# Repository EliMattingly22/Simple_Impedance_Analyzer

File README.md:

# Simple Impedance Analyzer

## Purpose

The impedance analyzer was designed as a low-cost, flexible, and accurate platform to perform impedance measurement at arbitrary frequencies up to ~250kHz. The current infrastructure assumes the user has access to a National Instruments DAQ (e.g. NI-USB-6363), though similar digitizers would be similarly effective. 

In this current configuration:
* About 0.1% Accuracy for large impedance and frequency ranges.
* The LabView has an easy to use GUI
* TDMS file saving
* It can measure impedances from 10mOhms to 10MOhms, and by changing the shunt resistor values that range could be extended 
* Test at frequencies from DC-250kHz (>100kHz still needs validation)
* Perform frequency sweeps on log or linear spacing
* If a battery-powered computer and DAQ is used, the entire measurement apparatus can be both portable and floating.

### Accuracy and noise (1 kHz resistive)

### Accuracy and noise (10 kHz resistive)

### Accuracy and noise (100 kHz resistive)

### Accuracy and noise (10 kHz Capacitors)

* It seems one can expect about 1% accuracy between 10 p to 0.1 mF. 
* The point indicating 0.01% accuracy is probably spurious. Some random errors happened to offset each others. 

# PCB
Use V2 rev B. V3 has not been tested/built. it is still in design phase. Perhaps it should just be in a separate brach of Github. Designed in KiCAD v6.

# Operating Principle
This circuit uses the "auto-balancing bridge" technique. If you are curious/want to play around with the circuit you can see the LTSPICE schematic. 

It is worth reading the [Keysight impedance measurement handbook](https://www.keysight.com/us/en/assets/7018-06840/application-notes/5950-3000.pdf) or TI's reference design for an LCR meter front-end for an overview of measurement techniques. 

The current through the DUT is (ideally) the same as the current in the shunt resistor, so the impedance is V(DUT) / (V(Shunt)/R(Shunt)). 

# Source of Errors

The precision of the circuit is dominated by the shunt resistors and gain accuracy of the INAs. Error in any of these will linearly cause an error in the calculated impedance. If they are stable over time, they can conceivably be calibrated with a high tolerance (e.g. 0.01%) reference resistor.

If the shunt resistor is off by some value, *X* (where 1.01 would be 1% higher than nominal), the current would be reported as I<sub>0</sub>**X* where I<sub>0</sub> is the actual current. 

The noise performance of the INAs isn't great, but the FET inputs have extremely low bias currents, and low current noise, which are necessary if high impedance loads are attached. The noise should add an incoherent error, so by averaging for longer, this can be mitigated. 

The parasitic elements can be accounted for by taking an open/short/load measurement. See sect. 4.3.2 in the impedance measurement handbook

# Operation instructions
## Setup
The device should be plugged in with a four-wire (Kelvin) probe attached. On the probe there will be two pairs of leads, each connected to a clamp (typically one pair is red, one is black). The two BNC connections on the red lead should be plugged into the "HPot" and "HCur" connectors, and the BNCs on the black probe should be connected to "LPot" and "HPot" connectors. 

Plug in the power and make sure the LEDs next to the "+5V" and "-5V" are illuminated. 

The DAQ should be plugged in via the BNC connectors and however they are connected, those outputs/inputs are selected on the front page of the Labview GUI.

Also on the front page, set the sampling rate to the maximum allowable (see documentation for your DAQ). Set the sampling time to be >10 periods of whatever frequency you are testing at. Longer gives better noise performance.

For the shunt resistor, use the value most similar to the load you are measuring. Use J13/14 to select the shunt resistor. 

Set the series resistor before the load (R9/24) to the same value as the shunt resistor using J17.

* For the saving cluster the Fine Name String will be the identifier in the file name.
* Save path is the directory it will be saved within
* Experiment title is a string added to the metadata
* Meta-data array is an array that the user can fill in as desired. It just goes into meta-data as-is. For example, if you are measuring the turns on an inductor vs inductance, you could enter the turn count in this spot and then afterwards when processing the data it would already be saved. 

* **Test Freq:** This is the measurement frequency for single measurements and stats. It is overwritten for frequency sweeps.
* **Output Signal Amp:** This is the waveform amplitude the DAQ outputs. If this is too low, SNR is sacrificed, if it is too high, the waveform can clip. Check the debugging cluster to ensure the amplitude of the voltage monitor and current monitor arent clipping (i.e. they are less than 7 V or so)
* **Sampling time:** Time of acquisition in seconds. Should be long enough for 10 or so periods of the output waveform. More improves SNR. 
* **Sampling Rate:** Sampling rate in Hz. should be maximum allowable.
* **Output Channel:** The channel that goes into the Voltage Input BNC (top left in photo above)
* **Current Channel:** The channel that comes from the current sense BNC (Bottom left in photo above)
* **Voltage channel:** The channel that comes from the voltage sense BNC (middle left in photo above)
* **Trigger channel:** This should be set to the output start trigger, for example "/Dev2/ao/StartTrigger"
* **Number of runs:** this is the number of times the acquisition will be repeated and averaged.

* **R_Shunt:** The shunt resistor value (R14/18)
* **Rg_Vmon:** The gain-setting resistor for the voltage monitor (R12 or R8) 
* **Rg_Imon:** The gain-setting resistor for the current monitor (R11 or R7) 
* **ESL_Cal:** This value is set by the short circuit compensation and is enabled by the UseCorrection boolean
* **ESR_Cal:** This value is set by the short circuit compensation and is enabled by the UseCorrection boolean
* **Cp_Cal:** This value is set by the open circuit compensation and is enabled by the UseCorrection boolean
* **Rp_Cal:** This value is set by the open circuit compensation and is enabled by the UseCorrection boolean

* **UseCorrection:** enables the short/open compensation values. Typically set to TRUE (green illuminated)

* **RLoad:** This is the actual value of the load compensation resistor that one may use to calibrate gain errors of the system. 

* **RLoad_Meas:** This is the measured value of that load. To acquire this value, set RLoad and RLoad_Meas to 0 and then measure the known load and set this and the RLoad by typing in the appropriate values.

## Calibration

Set the equipment up to measure your load, and short the clips together. Next, go to the Short/Open compensation tab and press the "Acquire short" button. Open the clips and then do the open compensation.

## Measure load

Use the last page to do a single impedance measurement and ensure the load is similar to expected. Then use the stats page or freq sweep depending on what you want. 

## List of jumpers & their purpose
* J15/16 low-pass filters for the input. These clean the analog signal from the DAQ. They can generally be set to the highest frequency that the user plans to measure. Removing the jumper disconnects the filtering entirely.

* J10: The current monitor gain selection
* J12: Voltage monitor gain selection
* J13/14: Shunt resistor selection
* J17: Series resistor selection. This resistor in series with the load helps stability and makes the system more balanced. The resistor value should match the shunt resistor value.

# If you are having errors:
1) Make sure the channels are selected properly
2) Make sure BOTH sides of the clips are on the load
3) Make sure the BNCs are properly attached
4) The LEDs should be illuminated
5) The amplitude should be sufficiently low that it doesn't saturate the inputs/clip

# Example applications:

## Litz wire, air-core inductor

* The impedance is exactly as expected here for an inductor. Because Litz wire was used, the resistance is not a strong function of frequency. 
* The slope of the reactance is constant and proportional to frequency.

## Skin and proximity effect on inductor

This is a frequency sweep of a solenoid (~1 mm diameter) wound on a copper tube with a wall-thickness of ~1 mm. Quite a lot is happening with this load:
* Below 50 Hz or so, it is essentially a resistor, the inductive impedance is very small. 
* At 50-1k Hz, the solenoid's impedance has an increasing real component and decreasing inductance (decreasing slope of imag.). This occurs as the inductor couples more strongly into the copper tube. The inductance decreases because the magnetic field in the center of the tube is decreasing as the wall effectively shields it. 
* Between 1k and 10k Hz the resistance nearly plateaus and the inductance starts rising proportionally to frequency. Presumably at this point, the skin depth of the copper tube has been met, so the magnetic fields are not significantly penetrating to the center of the tube. 
* Above 10 kHz the skin depth of the wire is being reached and the AC-resistance is increasing as the effective copper area for current to flow in decreases.

## Resonant L-C

## Notch filter input

# Thoughts for improvement
* Make the shunt resistor digitally selectable
* Build a microcontroller-based interface for increased portability
* Improve system accuracy for high impedance loads
* Improve system accuracy for high frequencies
* Modify it such that it uses only one amplifier for both VMon and IMon and a relay to select which one. 
* Replace INA121 with a JFET INA (e.g. 3 opamp configuration)
* Implement transformer test jig

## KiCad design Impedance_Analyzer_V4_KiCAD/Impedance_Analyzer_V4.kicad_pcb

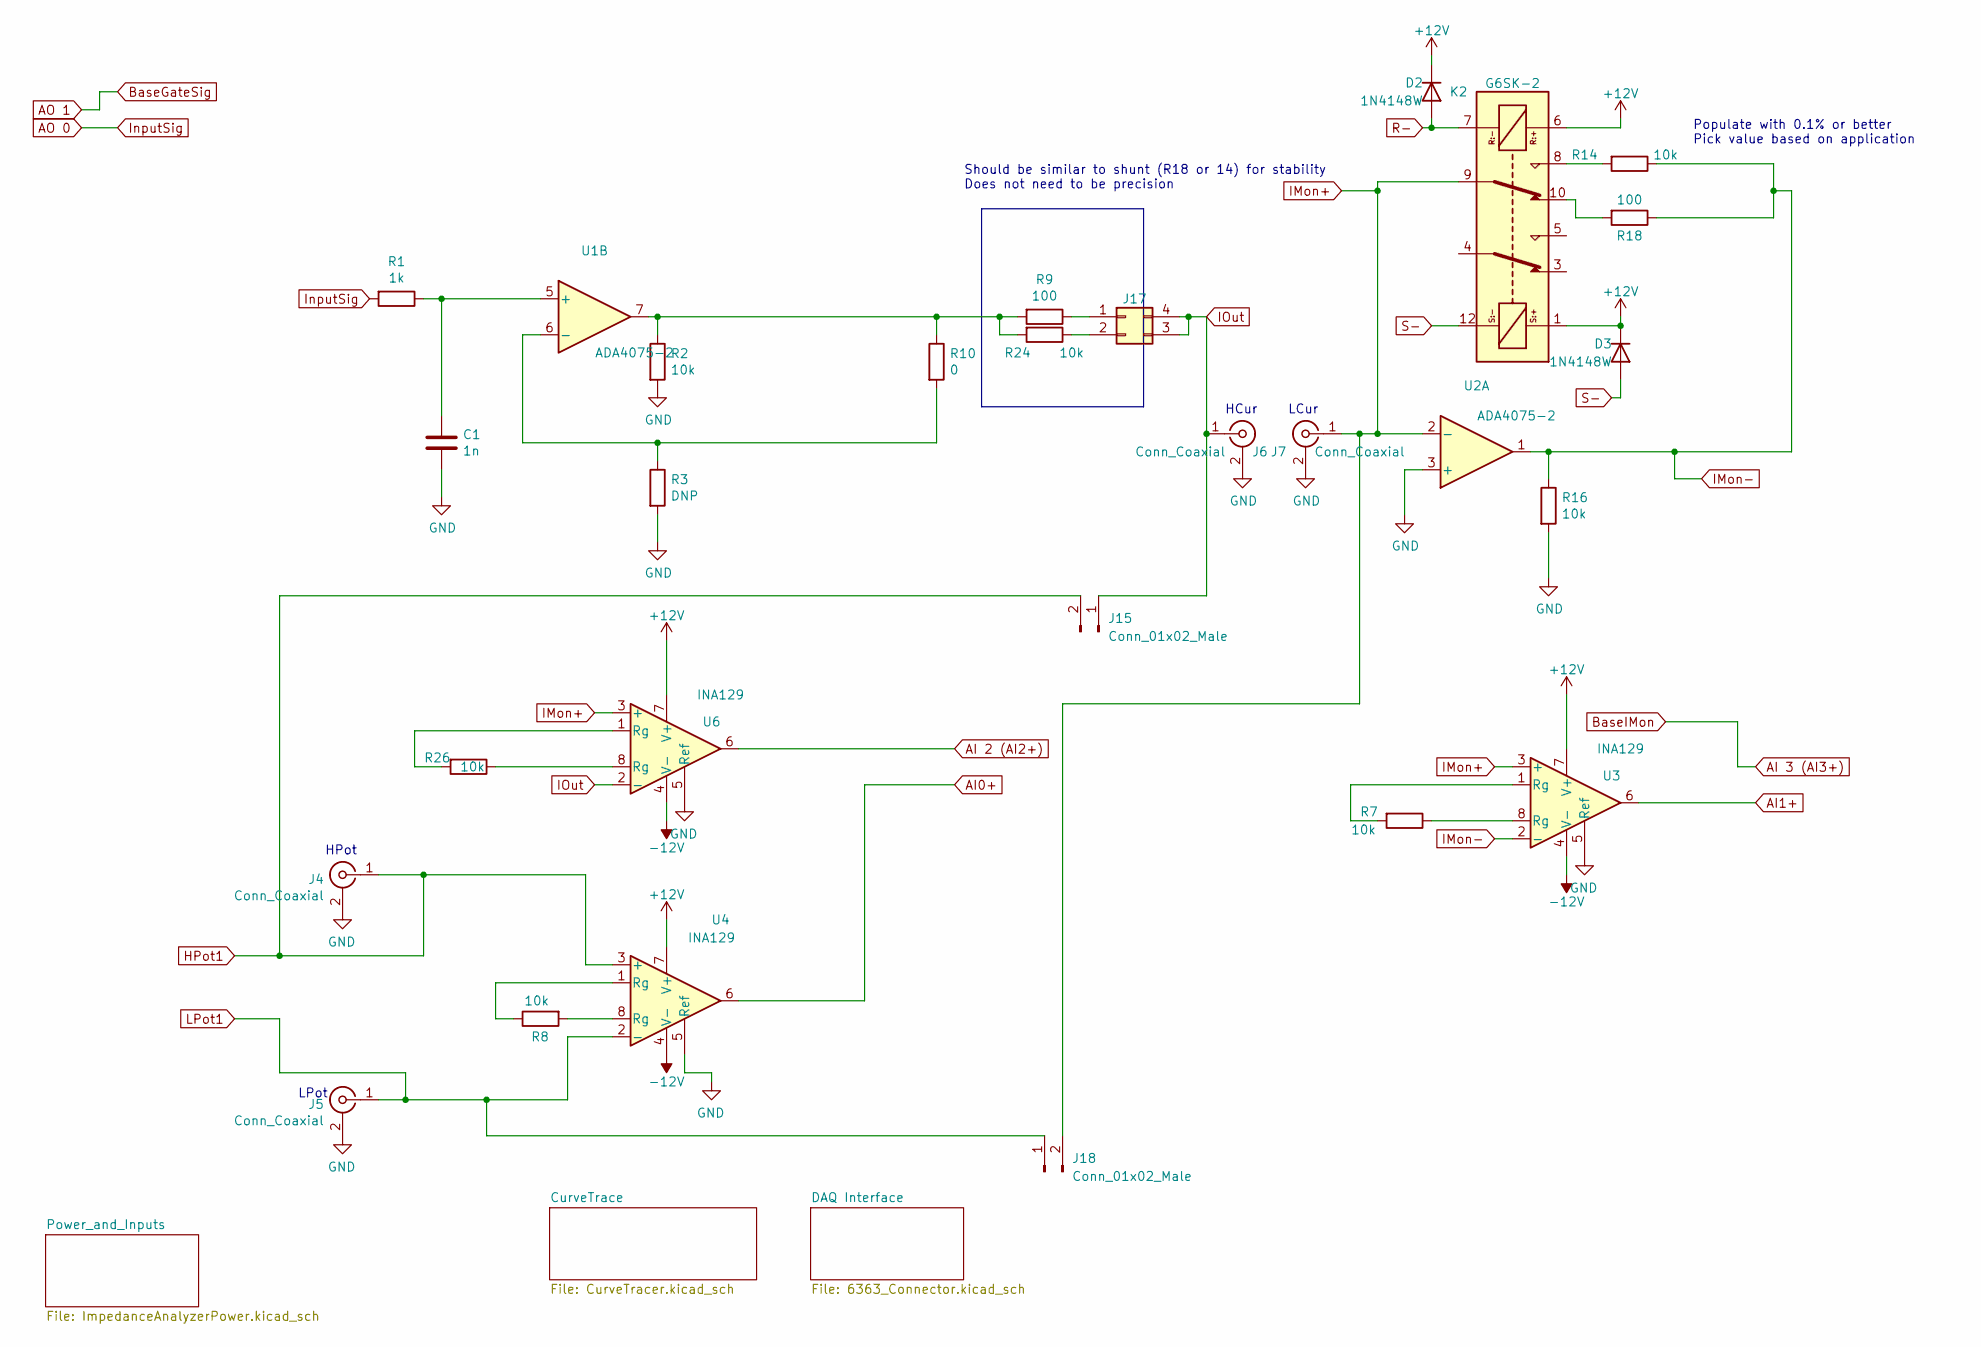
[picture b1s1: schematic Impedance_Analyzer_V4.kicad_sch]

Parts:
C1: 1n; C_0805_2012Metric
D2, D3: 1N4148W; D_SOD-123
J4, J5, J6, J7: Conn_Coaxial; 31-5486-1010 BNC Panel RA
J15, J18: Conn_01x02_Male; PinHeader_1x02_P2.54mm_Horizontal
J17: Conn_02x02_Counter_Clockwise; PinHeader_2x02_P2.54mm_Vertical
K2: G6SK-2; RELAY_G6SK-2F DC3_OMR
R1: 1k; R_1206_3216Metric
R2, R7, R8, R14, R16, R24, R26: 10k; R_1206_3216Metric
R3: DNP; R_1206_3216Metric
R9, R18: 100; R_1206_3216Metric
R10: 0; R_1206_3216Metric
U1, U2: ADA4075-2; SO-8_3.9x4.9mm_P1.27mm
U3, U4, U6: INA129; DIP-8_W7.62mm

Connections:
+12V: D2.1 (K), D3.1 (K), K2.1, K2.6, U3.7 (V+), U4.7 (V+), U6.7 (V+); also elsewhere on the board
-12V: U3.4 (V-), U4.4 (V-), U6.4 (V-); also elsewhere on the board
AI0+: U4.6; also elsewhere on the board
AI1+: U3.6; also elsewhere on the board
AI 2 (AI2+): U6.6; also elsewhere on the board
AO 0: R1.2; also elsewhere on the board
GND: C1.2, J4.2 (Ext), J5.2 (Ext), J6.2 (Ext), J7.2 (Ext), R2.2, R3.2, R16.2, U2.3 (+), U3.5 (Ref), U4.5 (Ref), U6.5 (Ref); also elsewhere on the board
HPot1: J4.1 (In), J15.2, U4.3 (+); also elsewhere on the board
IMon+: J7.1 (In), J18.2, K2.9, U2.2 (-), U3.3 (+), U6.3 (+)
IMon-: R14.1, R16.1, R18.1, U2.1, U3.2 (-)
IOut: J6.1 (In), J15.1, J17.3, J17.4, U6.2 (-)
LPot1: J5.1 (In), J18.1, U4.2 (-); also elsewhere on the board
unnamed: C1.1, R1.1, U1.5 (+)
unnamed: J17.1, R9.1
unnamed: J17.2, R24.1
unnamed: K2.8, R14.2
unnamed: K2.10, R18.2
unnamed: R7.1, U3.8 (Rg)
unnamed: R7.2, U3.1 (Rg)
unnamed: R8.1, U4.1 (Rg)
unnamed: R8.2, U4.8 (Rg)
unnamed: R2.1, R9.2, R10.1, R24.2, U1.7
unnamed: R3.1, R10.2, U1.6 (-)
unnamed: R26.1, U6.8 (Rg)
unnamed: R26.2, U6.1 (Rg)
R-: D2.2 (A), K2.7; also elsewhere on the board
S-: D3.2 (A), K2.12; also elsewhere on the board

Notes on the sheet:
HCur
Should be similar to shunt (R18 or 14) for stability Does not need to be precision
LCur
LPot
HPot
Populate with 0.1% or better Pick value based on application

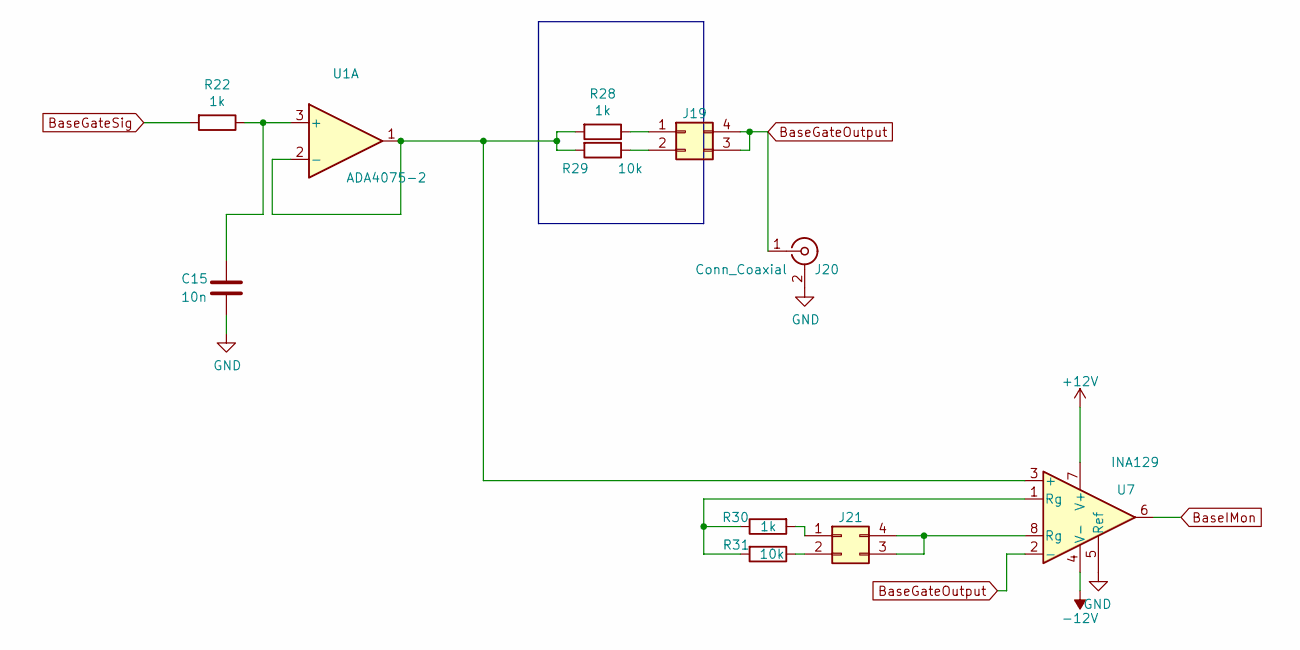
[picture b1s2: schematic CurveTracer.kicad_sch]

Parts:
C15: 10n; C_0805_2012Metric
J19, J21: Conn_02x02_Counter_Clockwise; PinHeader_2x02_P2.54mm_Vertical
J20: Conn_Coaxial; 31-5486-1010 BNC Panel RA
R22, R28, R30: 1k; R_1206_3216Metric
R29, R31: 10k; R_1206_3216Metric
U1: ADA4075-2; SO-8_3.9x4.9mm_P1.27mm
U7: INA129; DIP-8_W7.62mm

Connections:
+12V: U7.7 (V+); also elsewhere on the board
-12V: U7.4 (V-); also elsewhere on the board
BaseGateOutput: J19.3, J19.4, J20.1 (In), U7.2 (-)
GND: C15.2, J20.2 (Ext), U7.5 (Ref); also elsewhere on the board
unnamed: C15.1, R22.1, U1.3 (+)
unnamed: J19.1, R28.1
unnamed: J19.2, R29.1
unnamed: J21.1, R30.2
unnamed: J21.2, R31.1
unnamed: J21.3, J21.4, U7.8 (Rg)
unnamed: R28.2, R29.2, U1.1, U1.2 (-), U7.3 (+)
unnamed: R30.1, R31.2, U7.1 (Rg)

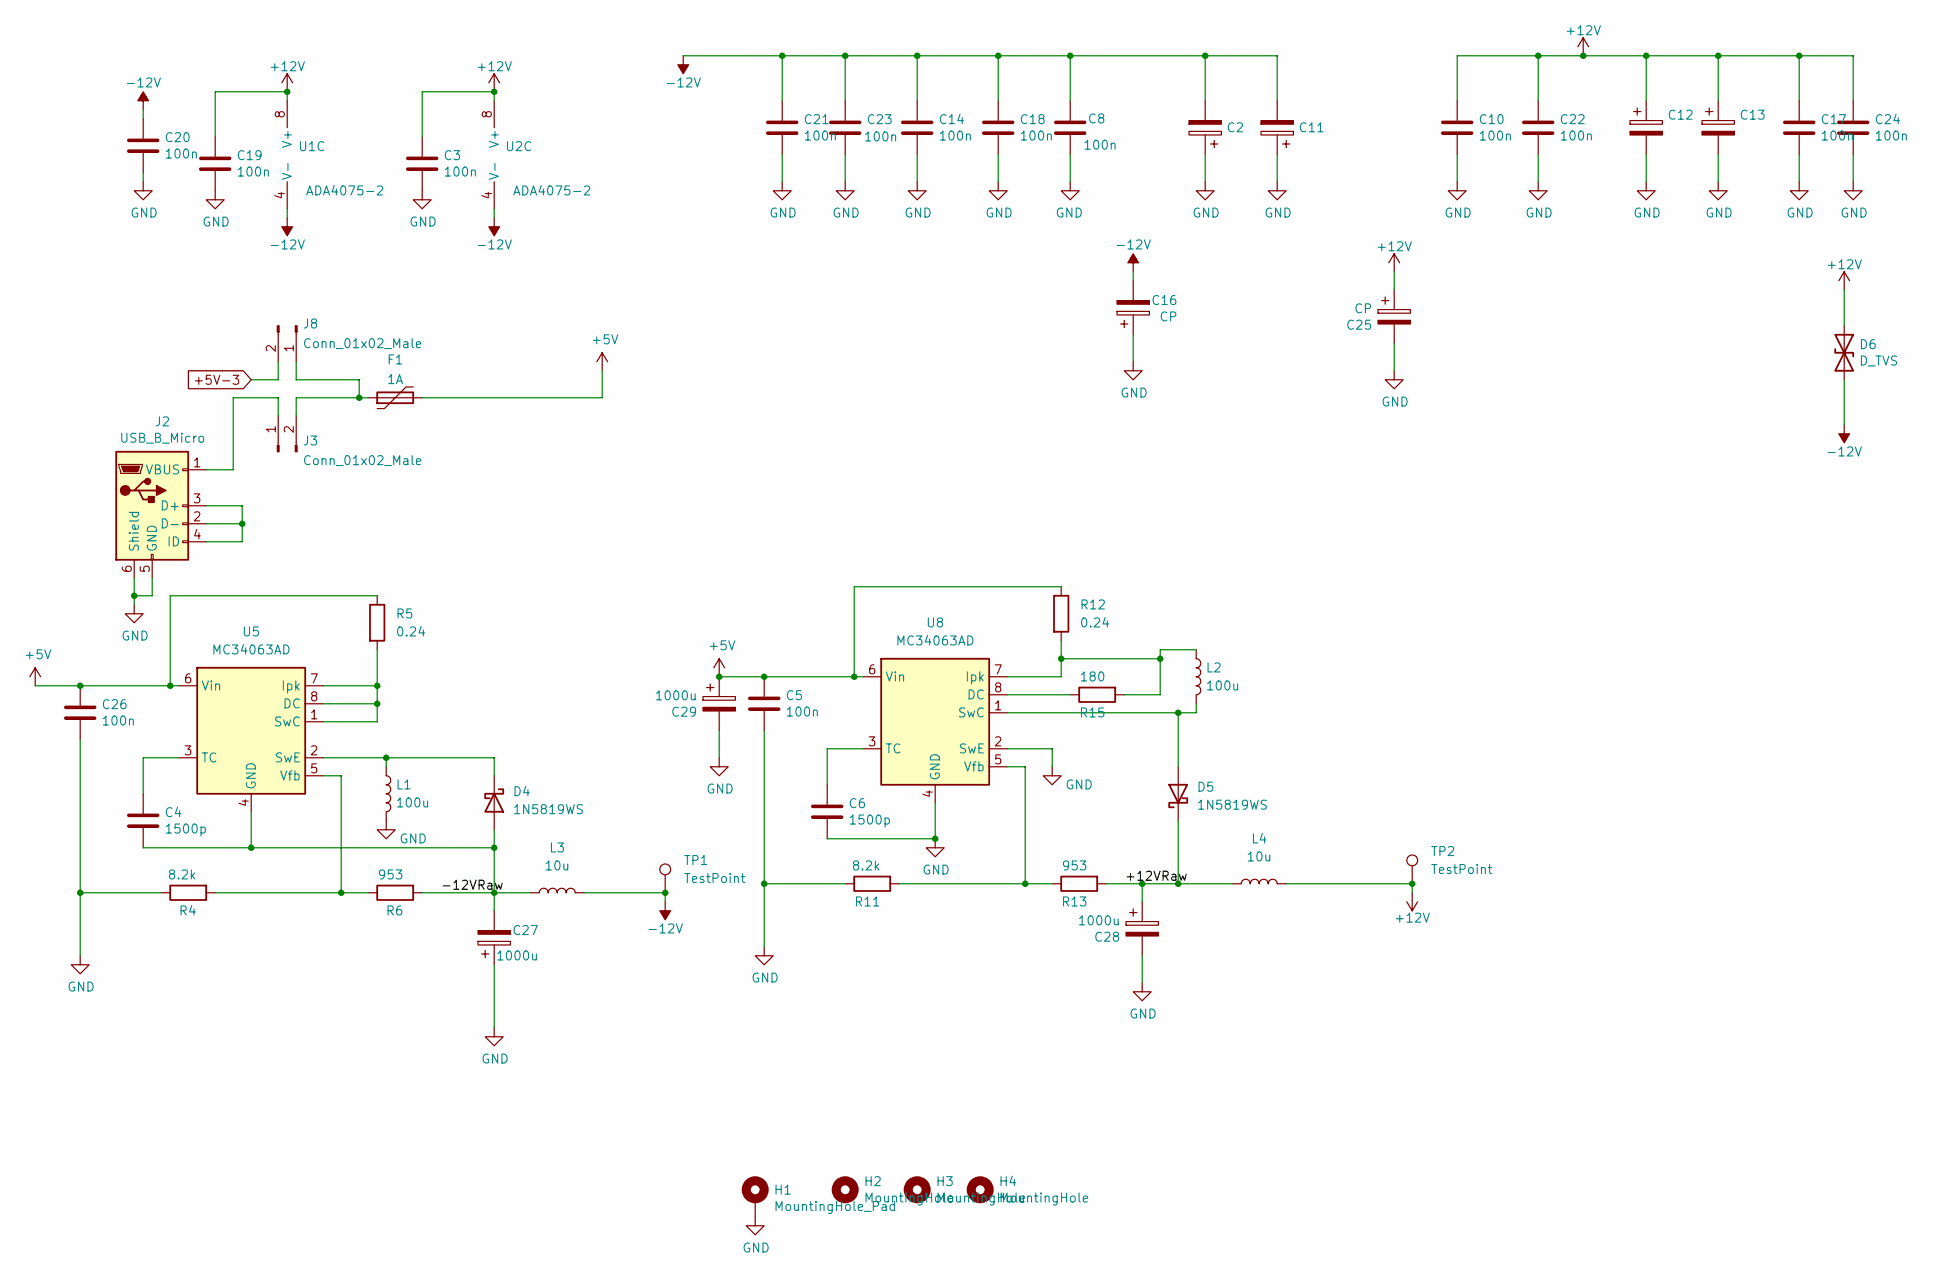
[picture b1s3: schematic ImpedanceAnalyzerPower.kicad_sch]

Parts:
C2, C11, C12, C13: C_Polarized; C_1206_3216Metric_Pad1.33x1.80mm_HandSolder
C3, C5, C8, C10, C14, C17, C18, C19, C20, C21, C22, C23, C24, C26: 100n; C_0805_2012Metric
C4, C6: 1500p; C_0805_2012Metric
C16, C25: CP; CP_Radial_D8.0mm_P5.00mm
C27, C28, C29: 1000u; CP_Elec_10x10.5
D4, D5: 1N5819WS; D_SOD-323
D6: D_TVS; D_SMA
F1: 1A; Fuse_1206_3216Metric_Pad1.42x1.75mm_HandSolder
H1: MountingHole_Pad; MountingHole_4.3mm_M4_Pad
H2, H3, H4: MountingHole; MountingHole_4mm
J2: USB_B_Micro; AMPHENOL_10118194-0001LF
J3, J8: Conn_01x02_Male; PinHeader_1x02_P2.54mm_Vertical
L1, L2: 100u; L_Taiyo-Yuden_NR-80xx_HandSoldering
L3, L4: 10u; L_Taiyo-Yuden_NR-60xx_HandSoldering
R4, R11: 8.2k; R_1206_3216Metric
R5, R12: 0.24; R_1206_3216Metric
R6, R13: 953; R_1206_3216Metric
R15: 180; R_1206_3216Metric
TP1, TP2: TestPoint; TestPoint_THTPad_2.0x2.0mm_Drill1.0mm
U1, U2: ADA4075-2; SO-8_3.9x4.9mm_P1.27mm
U5, U8: MC34063AD; SOIC-8_3.9x4.9mm_P1.27mm

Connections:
+5V: C5.1, C26.1, C29.1, F1.2, R5.1, R12.1, U5.6 (Vin), U8.6 (Vin); also elsewhere on the board
+5V-3: J8.2; also elsewhere on the board
+12V: C3.1, C10.1, C12.1, C13.1, C17.1, C19.1, C22.1, C24.1, C25.1, D6.1 (A1), L4.2, TP2.1, U1.8 (V+), U2.8 (V+); also elsewhere on the board
-12V: C2.2, C8.1, C11.2, C14.1, C16.2, C18.1, C20.1, C21.1, C23.1, D6.2 (A2), L3.2, TP1.1, U1.4 (V-), U2.4 (V-); also elsewhere on the board
/Power_and_Inputs/+12VRaw: C28.1, D5.1 (K), L4.1, R13.2
/Power_and_Inputs/-12VRaw: C4.2, C27.2, D4.2 (A), L3.1, R6.2, U5.4 (GND)
GND: C2.1, C3.2, C5.2, C6.2, C8.2, C10.2, C11.1, C12.2, C13.2, C14.2, C16.1, C17.2, C18.2, C19.2, C20.2, C21.2, C22.2, C23.2, C24.2, C25.2, C26.2, C27.1, C28.2, C29.2, H1.1, J2.5 (GND), J2.6 (Shield), L1.2, R4.1, R11.1, U8.2 (SwE), U8.4 (GND); also elsewhere on the board
unnamed: C4.1, U5.3 (TC)
unnamed: C6.1, U8.3 (TC)
unnamed: D4.1 (K), L1.1, U5.2 (SwE)
unnamed: D5.2 (A), L2.2, U8.1 (SwC)
unnamed: F1.1, J3.2, J8.1
unnamed: J2.1 (VBUS), J3.1
unnamed: J2.2 (D-), J2.3 (D+), J2.4 (ID)
unnamed: L2.1, R12.2, R15.2, U8.7 (Ipk)
unnamed: R4.2, R6.1, U5.5 (Vfb)
unnamed: R5.2, U5.1 (SwC), U5.7 (Ipk), U5.8 (DC)
unnamed: R11.2, R13.1, U8.5 (Vfb)
unnamed: R15.1, U8.8 (DC)

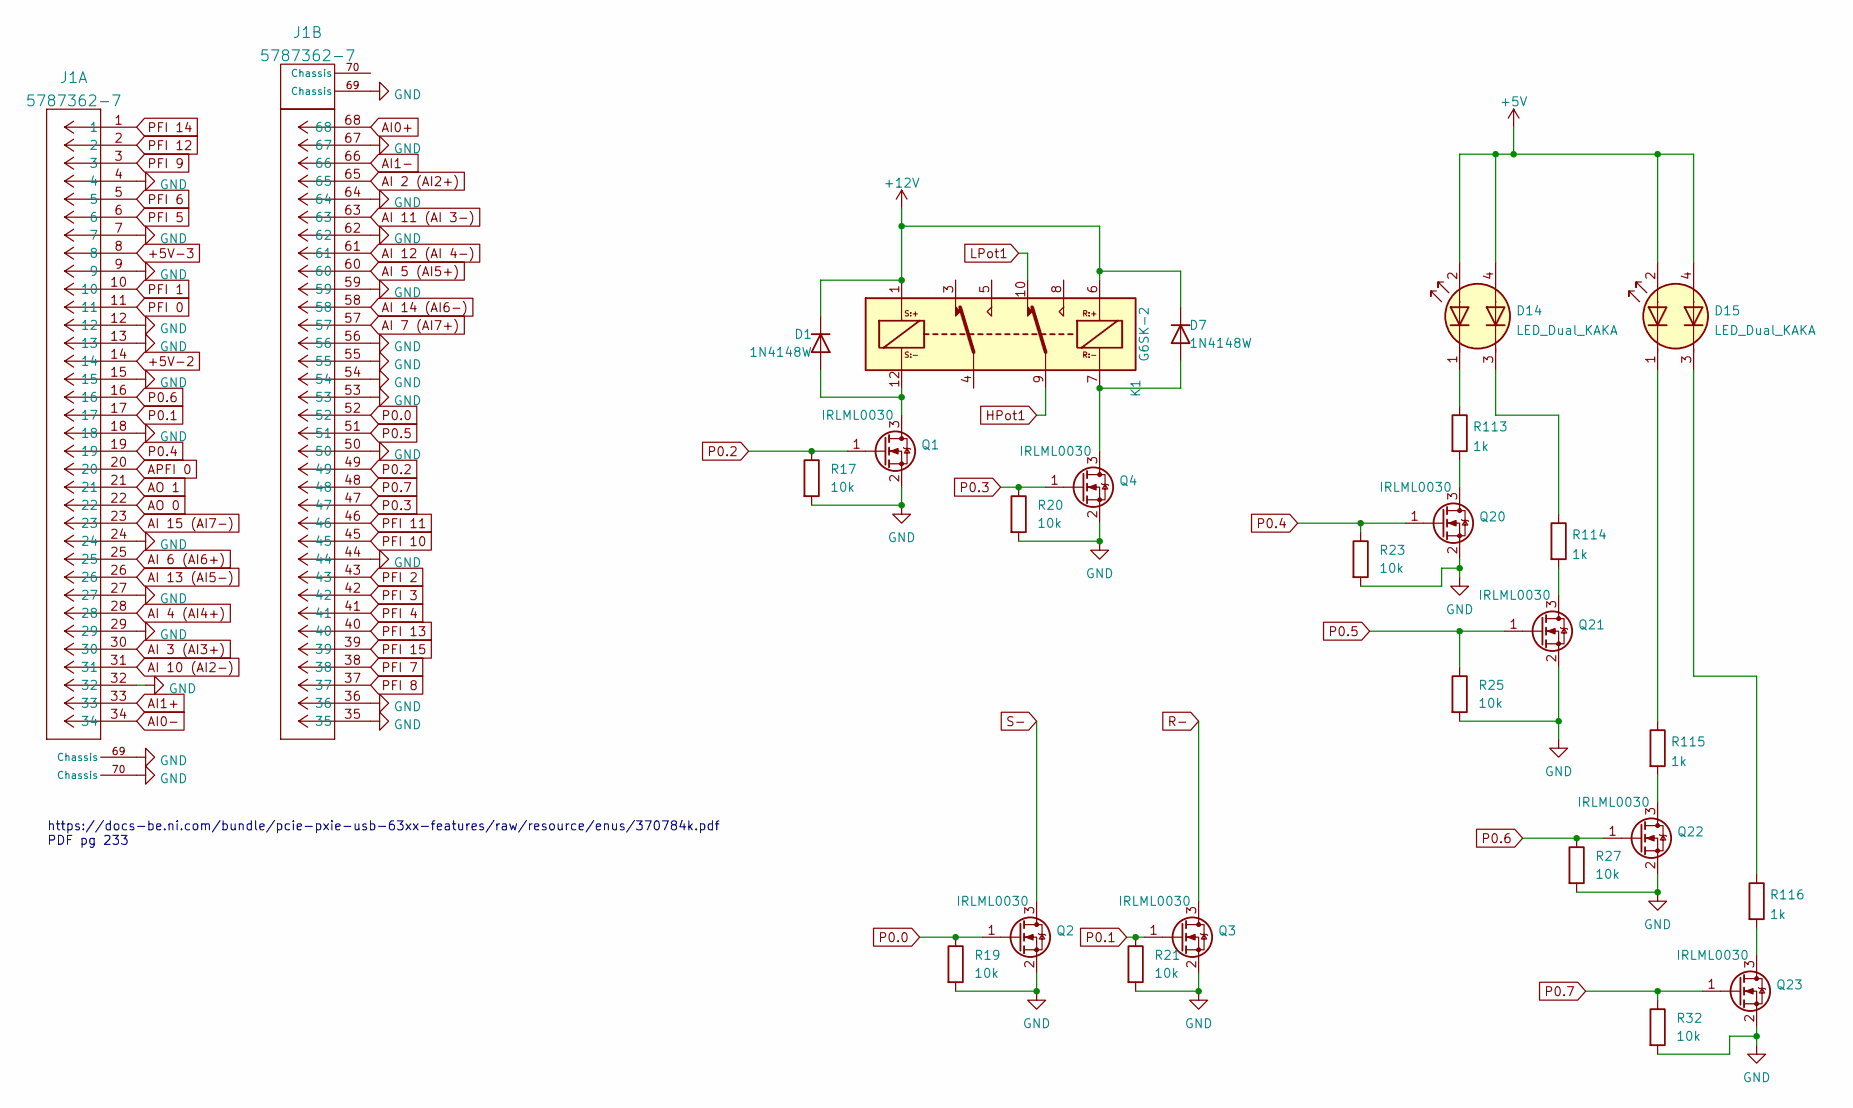
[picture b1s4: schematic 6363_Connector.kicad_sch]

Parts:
D1, D7: 1N4148W; D_SOD-123
D14, D15: LED_Dual_KAKA; IC4_WP934EB_2GD_KNB
J1: 5787362-7; 68DsubMaleTE_2-5174225-5
K1: G6SK-2; RELAY_G6SK-2F DC3_OMR
Q1, Q2, Q3, Q4, Q20, Q21, Q22, Q23: IRLML0030; SOT-23
R17, R19, R20, R21, R23, R25, R27, R32: 10k; R_0805_2012Metric_Pad1.20x1.40mm_HandSolder
R113, R114, R115, R116: 1k; R_0805_2012Metric_Pad1.20x1.40mm_HandSolder

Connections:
+5V: D14.2 (K1), D14.4 (K2), D15.2 (K1), D15.4 (K2); also elsewhere on the board
+5V-2: J1.14
+5V-3: J1.8; also elsewhere on the board
+12V: D1.1 (K), D7.1 (K), K1.1, K1.6; also elsewhere on the board
AI0+: J1.68; also elsewhere on the board
AI0-: J1.34
AI1+: J1.33; also elsewhere on the board
AI1-: J1.66
AI 2 (AI2+): J1.65; also elsewhere on the board
AI 4 (AI4+): J1.28
AI 5 (AI5+): J1.60
AI 6 (AI6+): J1.25
AI 7 (AI7+): J1.57
AI 10 (AI2-): J1.31
AI 11 (AI 3-): J1.63
AI 12 (AI 4-): J1.61
AI 13 (AI5-): J1.26
AI 14 (AI6-): J1.58
AI 15 (AI7-): J1.23
AO 0: J1.22; also elsewhere on the board
APFI 0: J1.20
GND: J1.4, J1.7, J1.9, J1.12, J1.13, J1.15, J1.18, J1.24, J1.27, J1.29, J1.32, J1.35, J1.36, J1.44, J1.50, J1.53, J1.54, J1.55, J1.56, J1.59, J1.62, J1.64, J1.67, J1.69 (Chassis), J1.70 (Chassis), Q1.2 (S), Q2.2 (S), Q3.2 (S), Q4.2 (S), Q20.2 (S), Q21.2 (S), Q22.2 (S), Q23.2 (S), R17.2, R19.2, R20.2, R21.2, R23.2, R25.2, R27.2, R32.2; also elsewhere on the board
HPot1: K1.9; also elsewhere on the board
LPot1: K1.10; also elsewhere on the board
unnamed: D1.2 (A), K1.12, Q1.3 (D)
unnamed: D7.2 (A), K1.7, Q4.3 (D)
unnamed: D14.1 (A1), R113.1
unnamed: D14.3 (A2), R114.1
unnamed: D15.1 (A1), R115.1
unnamed: D15.3 (A2), R116.1
unnamed: Q20.3 (D), R113.2
unnamed: Q21.3 (D), R114.2
unnamed: Q22.3 (D), R115.2
unnamed: Q23.3 (D), R116.2
P0.0: J1.52, Q2.1 (G), R19.1
P0.1: J1.17, Q3.1 (G), R21.1
P0.2: J1.49, Q1.1 (G), R17.1
P0.3: J1.47, Q4.1 (G), R20.1
P0.4: J1.19, Q20.1 (G), R23.1
P0.5: J1.51, Q21.1 (G), R25.1
P0.6: J1.16, Q22.1 (G), R27.1
P0.7: J1.48, Q23.1 (G), R32.1
PFI 0: J1.11
PFI 1: J1.10
PFI 2: J1.43
PFI 3: J1.42
PFI 4: J1.41
PFI 5: J1.6
PFI 6: J1.5
PFI 7: J1.38
PFI 8: J1.37
PFI 9: J1.3
PFI 10: J1.45
PFI 11: J1.46
PFI 12: J1.2
PFI 13: J1.40
PFI 14: J1.1
PFI 15: J1.39
R-: Q3.3 (D); also elsewhere on the board
S-: Q2.3 (D); also elsewhere on the board

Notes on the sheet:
https://docs-be.ni.com/bundle/pcie-pxie-usb-63xx-features/raw/resource/enus/370784k.pdf PDF pg 233

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
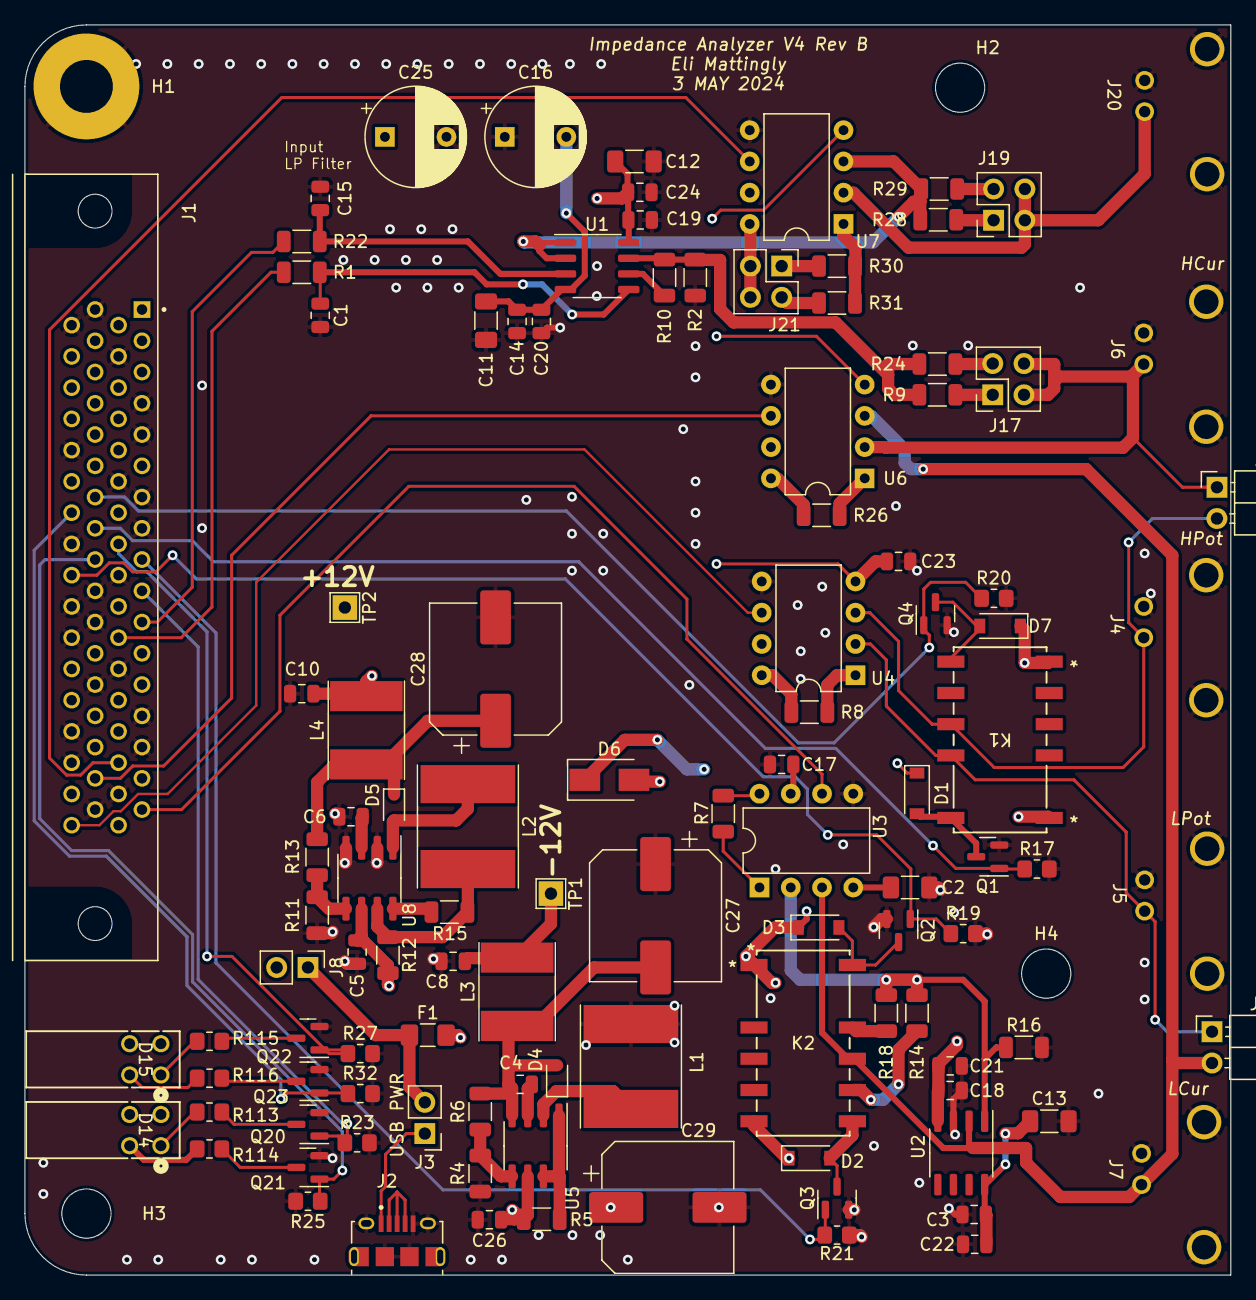
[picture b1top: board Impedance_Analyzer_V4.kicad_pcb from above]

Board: 4 copper layers, 98.0 x 101.6 mm, 114 parts (0 on the bottom side), 72 nets.

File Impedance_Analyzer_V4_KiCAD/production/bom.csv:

Designator,Footprint,Quantity,Value,LCSC Part #
C1,0805,1,1n,
C10,0805,1,100n,
C11,1206,1,C_Polarized,
C12,1206,1,C_Polarized,
C13,1206,1,C_Polarized,
C14,0805,1,100n,
C15,0805,1,10n,
"C16, C25",CP_Radial_D8.0mm_P5.00mm,2,CP,
C17,0805,1,100n,
C18,0805,1,100n,
C19,0805,1,100n,
C2,1206,1,C_Polarized,
C20,0805,1,100n,
C21,0805,1,100n,
C22,0805,1,100n,
C23,0805,1,100n,
C24,0805,1,100n,
C26,0805,1,100n,
"C27, C28, C29",CP_Elec_10x10.5,3,1000u,
C3,0805,1,100n,
C4,0805,1,1500p,
C5,0805,1,100n,
C6,0805,1,1500p,
C8,0805,1,100n,
"D1, D2, D3, D7",D_SOD-123,4,1N4148W,
"D14, D15",IC4_WP934EB_2GD_KNB,2,LED_Dual_KAKA,
"D4, D5",D_SOD-323,2,1N5819WS,
D6,D_SMA,1,D_TVS,
F1,1206,1,1A,
H1,MountingHole_4.3mm_M4_Pad,1,MountingHole_Pad,
"H2, H3, H4",MountingHole_4mm,3,MountingHole,
J1,68DsubMaleTE_2-5174225-5,1,5787362-7,
"J15, J18",PinHeader_1x02_P2.54mm_Horizontal,2,Conn_01x02_Male,
"J17, J19, J21",PinHeader_2x02_P2.54mm_Vertical,3,Conn_02x02_Counter_Clockwise,
J2,AMPHENOL_10118194-0001LF,1,USB_B_Micro,
"J20, J4, J5, J6, J7",31-5486-1010 BNC Panel RA,5,Conn_Coaxial,
"J3, J8",PinHeader_1x02_P2.54mm_Vertical,2,Conn_01x02_Male,
"K1, K2",RELAY_G6SK-2F DC3_OMR,2,G6SK-2,
"L1, L2",L_Taiyo-Yuden_NR-80xx_HandSoldering,2,100u,
"L3, L4",L_Taiyo-Yuden_NR-60xx_HandSoldering,2,10u,
"Q1, Q2, Q20, Q21, Q22, Q23, Q3, Q4",SOT-23,8,IRLML0030,
R1,1206,1,1k,
R10,1206,1,0,
R11,1206,1,8.2k,
R113,0805,1,1k,
R114,0805,1,1k,
R115,0805,1,1k,
R116,0805,1,1k,
R12,1206,1,0.24,
R13,1206,1,953,
R14,1206,1,10k,
R15,1206,1,180,
R16,1206,1,10k,
R17,0805,1,10k,
R18,1206,1,100,
R19,0805,1,10k,
R2,1206,1,10k,
R20,0805,1,10k,
R21,0805,1,10k,
R22,1206,1,1k,
R23,0805,1,10k,
R24,1206,1,10k,
R25,0805,1,10k,
R26,1206,1,10k,
R27,0805,1,10k,
R28,1206,1,1k,
R29,1206,1,10k,
R30,1206,1,1k,
R31,1206,1,10k,
R32,0805,1,10k,
R4,1206,1,8.2k,
R5,1206,1,0.24,
R6,1206,1,953,
R7,1206,1,10k,
R8,1206,1,10k,
R9,1206,1,100,
"TP1, TP2",TestPoint_THTPad_2.0x2.0mm_Drill1.0mm,2,TestPoint,
"U1, U2",SO-8_3.9x4.9mm_P1.27mm,2,ADA4075-2,
"U3, U4, U6, U7",DIP-8_W7.62mm,4,INA129,
"U5, U8",SOIC-8_3.9x4.9mm_P1.27mm,2,MC34063AD,

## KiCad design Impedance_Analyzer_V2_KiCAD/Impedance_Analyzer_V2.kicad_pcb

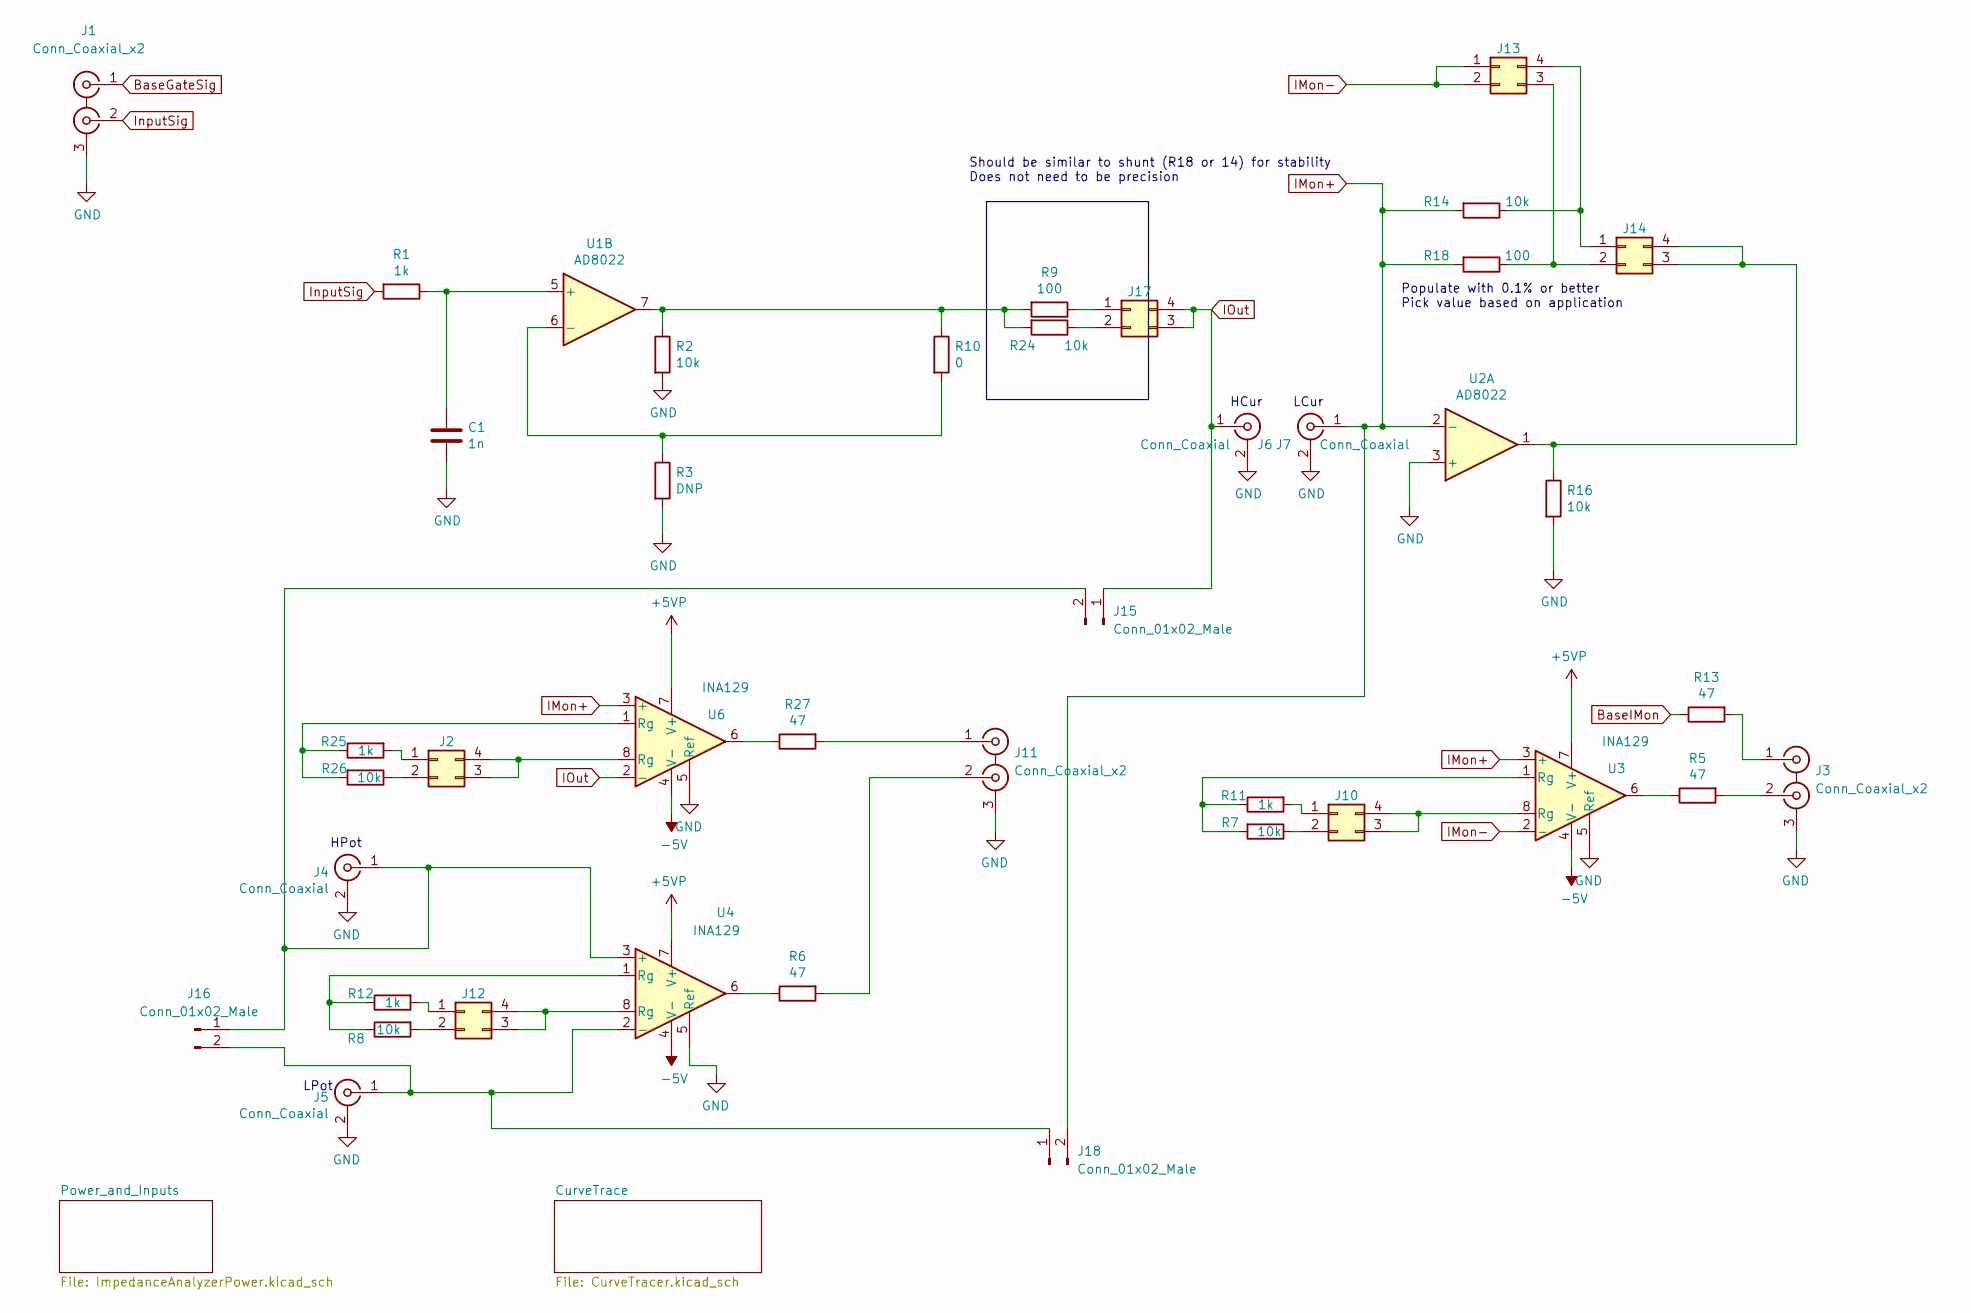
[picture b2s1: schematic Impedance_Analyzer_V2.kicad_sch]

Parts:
C1: 1n; C_0805_2012Metric
J1, J3, J11: Conn_Coaxial_x2; BNC_Win_364A2x95_Horizontal
J2, J10, J12, J13, J14, J17: Conn_02x02_Counter_Clockwise; PinHeader_2x02_P2.54mm_Vertical
J4, J5, J6, J7: Conn_Coaxial; 31-5486-1010 BNC Panel RA
J15, J16, J18: Conn_01x02_Male; PinHeader_1x02_P2.54mm_Horizontal
R1, R11, R12, R25: 1k; R_1206_3216Metric
R2, R7, R8, R14, R16, R24, R26: 10k; R_1206_3216Metric
R3: DNP; R_1206_3216Metric
R5, R6, R13, R27: 47; R_1206_3216Metric
R9, R18: 100; R_1206_3216Metric
R10: 0; R_1206_3216Metric
U1, U2: AD8022; SO-8_3.9x4.9mm_P1.27mm
U3, U4, U6: INA129; DIP-8_W7.62mm

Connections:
+5VP: U3.7 (V+), U4.7 (V+), U6.7 (V+); also elsewhere on the board
-5V: U3.4 (V-), U4.4 (V-), U6.4 (V-); also elsewhere on the board
BaseGateSig: J1.1 (IN1); also elsewhere on the board
BaseIMon: R13.1; also elsewhere on the board
GND: C1.2, J1.3 (EXT), J3.3 (EXT), J4.2 (Ext), J5.2 (Ext), J6.2 (Ext), J7.2 (Ext), J11.3 (EXT), R2.2, R3.2, R16.2, U2.3 (+), U3.5 (Ref), U4.5 (Ref), U6.5 (Ref); also elsewhere on the board
IMon+: J7.1 (In), J18.2, R14.2, R18.2, U2.2 (-), U3.3 (+), U6.3 (+)
IMon-: J13.1, J13.2, U3.2 (-)
IOut: J6.1 (In), J15.1, J17.3, J17.4, U6.2 (-)
InputSig: J1.2 (IN2), R1.2
unnamed: C1.1, R1.1, U1.5 (+)
unnamed: J2.1, R25.2
unnamed: J2.2, R26.1
unnamed: J2.3, J2.4, U6.8 (Rg)
unnamed: J3.1 (IN1), R13.2
unnamed: J3.2 (IN2), R5.2
unnamed: J5.1 (In), J16.2, J18.1, U4.2 (-)
unnamed: J10.1, R11.2
unnamed: J10.2, R7.1
unnamed: J10.3, J10.4, U3.8 (Rg)
unnamed: J11.1 (IN1), R27.2
unnamed: J11.2 (IN2), R6.2
unnamed: J12.1, R12.2
unnamed: J12.2, R8.2
unnamed: J12.3, J12.4, U4.8 (Rg)
unnamed: J13.3, J14.2, R18.1
unnamed: J13.4, J14.1, R14.1
unnamed: J14.3, J14.4, R16.1, U2.1
unnamed: J4.1 (In), J15.2, J16.1, U4.3 (+)
unnamed: J17.1, R9.1
unnamed: J17.2, R24.1
unnamed: R5.1, U3.6
unnamed: R6.1, U4.6
unnamed: R2.1, R9.2, R10.1, R24.2, U1.7
unnamed: R3.1, R10.2, U1.6 (-)
unnamed: R7.2, R11.1, U3.1 (Rg)
unnamed: R8.1, R12.1, U4.1 (Rg)
unnamed: R25.1, R26.2, U6.1 (Rg)
unnamed: R27.1, U6.6

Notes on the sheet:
HCur
Should be similar to shunt (R18 or 14) for stability Does not need to be precision
LCur
LPot
HPot
Populate with 0.1% or better Pick value based on application
